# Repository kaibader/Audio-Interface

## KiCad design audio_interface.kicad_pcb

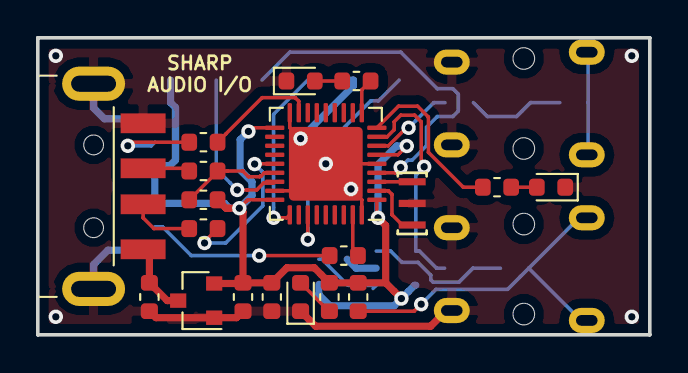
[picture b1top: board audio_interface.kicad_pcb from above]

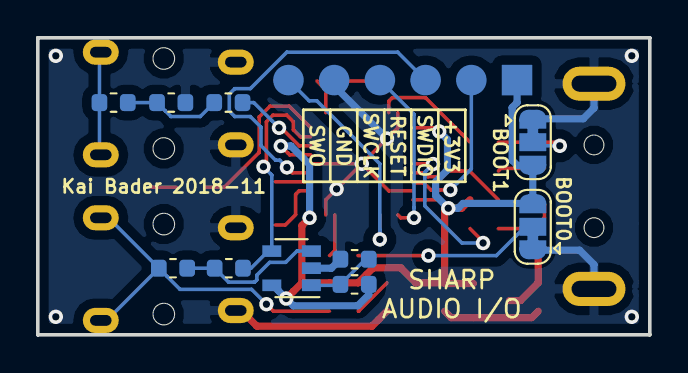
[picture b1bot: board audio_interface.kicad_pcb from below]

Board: 2 copper layers, 34.0 x 16.5 mm, 33 parts (11 on the bottom side), 29 nets.

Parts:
C1, C2: 1u; C_0603_1608Metric
C3: 10n; C_0603_1608Metric
C4, C5: 0.1u; C_0603_1608Metric
C6: 10u; C_0603_1608Metric
D1, D3: Status LED; LED_0603_1608Metric
D2: Power LED; LED_0603_1608Metric
H1: Soundcard Case; USB_Soundcard_Case
J1: USB_A; USB-A-Connector
J2: SWD; PinHeader_SMD_1x06
J3: EAR; Audio_Jack_3.5mm_Horizontal
J4: MIC; Audio_Jack_3.5mm_Horizontal
JP1: B0; SolderJumper-3_P1.3mm_Bridged12_RoundedPad1.0x1.5mm
JP2: B1; SolderJumper-3_P1.3mm_Bridged12_RoundedPad1.0x1.5mm
R1, R2: 22; R_0603_1608Metric
R3, R5, R8, R10: 10k; R_0603_1608Metric
R4: 1.5k; R_0603_1608Metric
R6: 200k; R_0603_1608Metric
R7: 20k; R_0603_1608Metric
R9: 1.8k; R_0603_1608Metric
R11, R12, R13: 510; R_0603_1608Metric
U1: STM32F103T8Ux; QFN-36-1EP_6x6mm_P0.5mm_EP4.1x4.1mm
U2: XC6206; SOT-23
U3: LMV321; SOT-23-5
Y1: CSTCE8M00G52

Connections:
+3V3: C2.1, C3.1, J2.1, JP1.3, JP2.3, R4.1, R7.1, R10.1, R12.2, U1.1, U1.6, U1.19, U1.27, U2.2, U3.5
/BOOT0: R3.1, U1.35
/BOOT1: R5.2, U1.17
/LED1: R11.2, U1.9
/LED2: R13.2, U1.10
/LINE_OUT: R9.2, U1.7
/MIC_IN: R6.1, U1.8, U3.4
/SWCLK: J2.4, U1.28
/SWDIO: J2.2, U1.25
/SWO: J2.6, U1.30
/USB_DM: R2.1, U1.23
/USB_DP: R1.1, R4.2, U1.24
/~RESET: J2.3, U1.4
GND: C1.2, C2.2, C3.2, C5.2, D1.1, D2.1, D3.1, J1.4, J1.5, J2.5, J3.R, J3.S, J4.R, J4.S, JP1.1, JP2.1, R8.2, U1.5, U1.18, U1.26, U1.36, U1.37, U2.1, U3.2, Y1.2
unnamed: C4.1, R6.2, U3.3
unnamed: C4.2, J4.T, R10.2
unnamed: C5.1, C6.2, R9.1
unnamed: C6.1, J3.T
unnamed: D1.2, R11.1
unnamed: D2.2, R12.1
unnamed: D3.2, R13.1
unnamed: J1.2, R2.2
unnamed: J1.3, R1.2
unnamed: JP1.2, R3.2
unnamed: JP2.2, R5.1
unnamed: R7.2, R8.1, U3.1
unnamed: U1.2, Y1.1
unnamed: U1.3, Y1.3
VBUS: C1.1, J1.1, U2.3

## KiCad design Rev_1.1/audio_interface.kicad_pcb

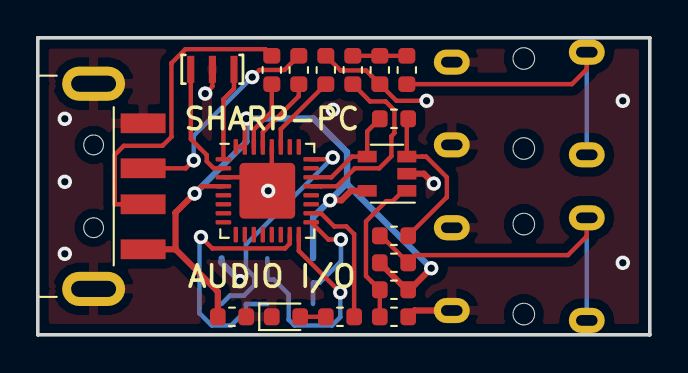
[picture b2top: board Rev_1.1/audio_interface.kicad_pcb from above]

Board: 2 copper layers, 34.0 x 16.5 mm, 21 parts (1 on the bottom side), 22 nets.

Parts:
C1, C3, C4: 0.1u; C_0603_1608Metric
C2: 1u; C_0603_1608Metric
C5: 10u; C_0603_1608Metric
D1: Status LED; LED_0603_1608Metric
J1: USB_A; USB-A-Connector
J2: AVR-ISP (SMD); Pin_Header_SMD_2x03
J3: LINE-OUT; Audio_Jack_3.5mm_Horizontal
J4: MIC-IN; Audio_Jack_3.5mm_Horizontal
R1, R2: 22; R_0603_1608Metric
R3: 470; R_0603_1608Metric
R4: 200k; R_0603_1608Metric
R5: 20k; R_0603_1608Metric
R6, R8: 10k; R_0603_1608Metric
R7: 1.8k; R_0603_1608Metric
U1: ATmega32U2-AU; ATmega32U2-AU-QFN-32
U2: LMV321; SOT-23-5
Y1: CSTCE16M0V53MU; CSTCE16M0V

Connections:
/LED: R3.1, U1.18
/LINE-OUT: R7.2, U1.21
/MIC-IN: R4.1, U1.22, U2.4
/MISO: J2.1, U1.17
/MOSI: J2.4, U1.16
/SCK: J2.3, U1.15
/Y+: U1.1, Y1.1
/Y-: U1.2, Y1.3
/~RESET: J2.5, U1.24
GND: C1.2, C2.2, C4.2, D1.1, J1.4, J1.5, J2.6, J3.R, J3.S, J4.R, J4.S, R6.2, U1.3, U1.28, U1.33, U2.2, Y1.2
unnamed: C2.1, U1.27
unnamed: C3.1, R4.2, U2.3
unnamed: C3.2, J4.T, R8.2
unnamed: C4.1, C5.2, R7.1
unnamed: C5.1, J3.T
unnamed: D1.2, R3.2
unnamed: J1.2, R2.2
unnamed: J1.3, R1.2
unnamed: R1.1, U1.29
unnamed: R2.1, U1.30
unnamed: R5.2, R6.1, U2.1
VBUS: C1.1, J1.1, J2.2, R5.1, R8.1, U1.4, U1.31, U1.32, U2.5

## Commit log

2016-04-13 Initial commit (ignore list).
2016-04-13 Created a new KiCAD project for my 'Sharp PC-1500 Audio Interface'
2016-04-13 Added LTspice test files
2016-04-13 Repo cleanup
2016-04-13 Panelized PCB. Added Gerber files.
2016-04-16 Clean-up
2017-05-25 Added (part cache) library
2018-09-07 Moved/Saved the current state of the project into a v1.0 folder for documentation purposes.
    - Exported the Symbols into a separate lib for backup reasons.
    - Imported the project from KiCad v4 into KiCad v5 (as good as possible).
    - Updated the ignore list.
2018-09-20 Various changes / refactoring.
    - Updated the schematic due to KiCad 5 changes.
    - Reorganized the directories to allow better version control.
    - Cleaned up the LTspice files and created new ones (better fitting ones) for the Sharp PC-1500.
2018-10-17 Squashed commit. Worked on an Rev_1.1 Audio Interface with various changes/updates.
2018-10-19 Moved v1.0 to Rev_1.0
2018-10-19 Rev_1.1 Preparation
2018-10-19 Rev_1.1
2018-10-23 Revision Clean-Up
2018-11-08 Rev 2.0 based on an STM32F103 microcontroller.
